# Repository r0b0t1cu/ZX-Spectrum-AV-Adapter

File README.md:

# ZX Spectrum Composite Mod PCB

This is a small replacement board for the original RF modulator found in the ZX Spectrum.
It provides a clean composite video output while keeping the installation simple and reversible.

Designed as a drop-in replacement for the RF can on the new boards. Keep in mind the original board don't have large holes for the screws to go in.
Minimal component count. Improved video quality compared to the stock RF output.

You can choose via a jumper to have output through the capacitor or through a transistor.

---

If you enjoy my projects and would like to support my work, you can do so through PCBWay. You can also order the PCBs for this project directly from the link below. Every bit of support is appreciated!

<p>
  
</p>

---

Inspiration from here: https://blog.retroleum.co.uk/electronics-articles/repairing-a-zx-spectrum/spectrum-video-mods/

Gerber files are available in the **AV-Adapter/production/** folder.

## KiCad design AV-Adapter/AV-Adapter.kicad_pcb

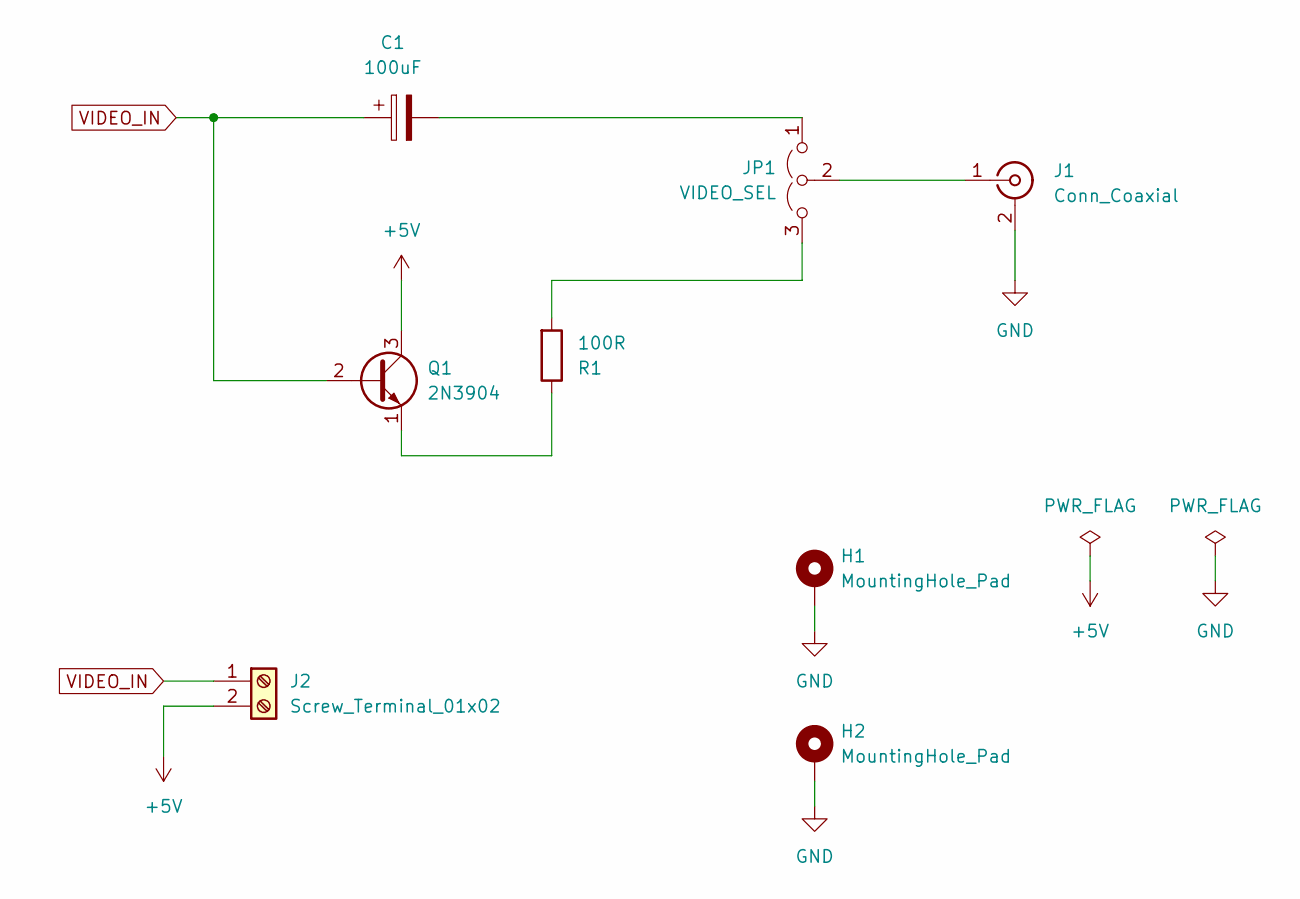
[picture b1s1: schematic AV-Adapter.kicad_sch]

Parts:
C1: 100uF; CP_Radial_D5.0mm_P2.50mm
H1, H2: MountingHole_Pad; MountingHole_3.2mm_M3_Pad
J1: Conn_Coaxial; RCA_CONNECTOR
J2: Screw_Terminal_01x02; TerminalBlock_Phoenix_MKDS-1,5-2-5.08_1x02_P5.08mm_Horizont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
JP1: VIDEO_SEL; PinHeader_1x03_P2.54mm_Vertical
Q1: 2N3904; TO-92_Wide
R1: 100R; R_Axial_DIN0207_L6.3mm_D2.5mm_P7.62mm_Horizontal

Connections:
+5V: J2.2, Q1.3 (C)
GND: H1.1, H2.1, J1.2 (Ext)
unnamed: J1.1 (In), JP1.2 (C)
unnamed: C1.2, JP1.1 (A)
unnamed: JP1.3 (B), R1.2
unnamed: Q1.1 (E), R1.1
VIDEO_IN: C1.1, J2.1, Q1.2 (B)

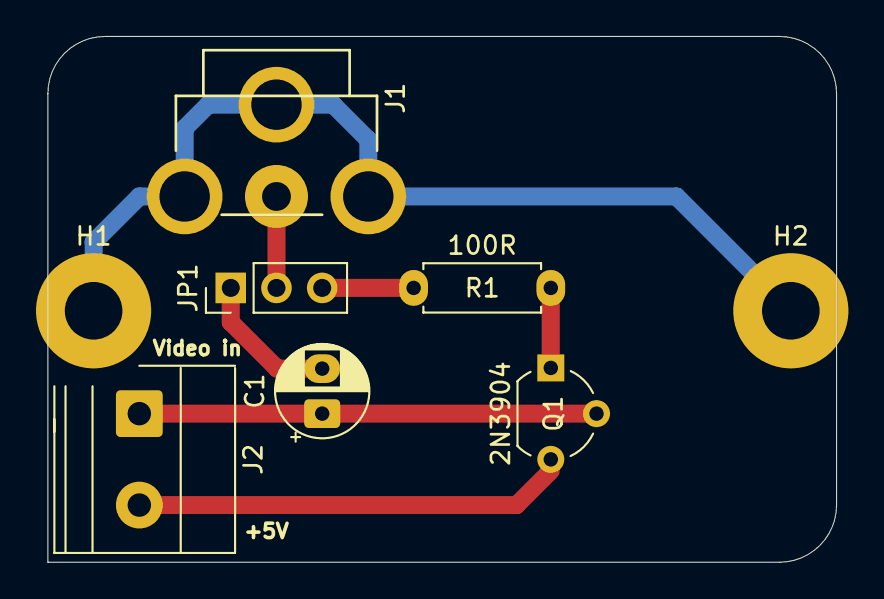
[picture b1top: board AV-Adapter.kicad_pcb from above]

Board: 2 copper layers, 43.8 x 29.2 mm, 8 parts (0 on the bottom side), 7 nets.

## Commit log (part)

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2025-12-05 Revise README with new title and detailed description
    Updated project title and expanded description with additional details about design, component count, and output options.
